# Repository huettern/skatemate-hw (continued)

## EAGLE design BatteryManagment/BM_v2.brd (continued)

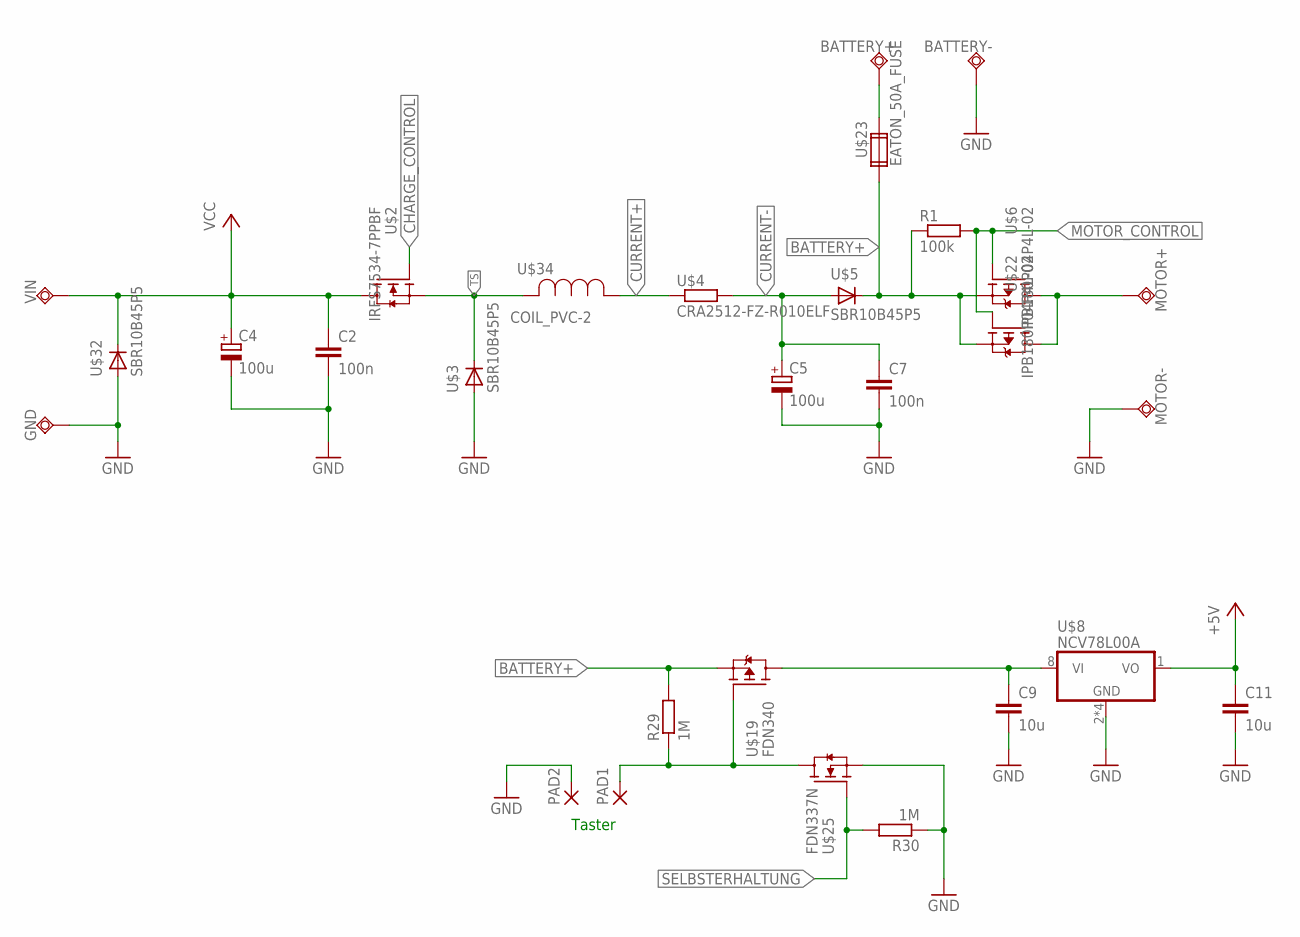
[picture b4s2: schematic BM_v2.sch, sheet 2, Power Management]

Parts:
BATTERY+: Battery+; TESTPAD
BATTERY-: Battery+; TESTPAD
C2, C7: 100n; C0603
C4, C5: 100u; E3,5-10
C9, C11: 10u; C0805
GND: Battery+; TESTPAD
MOTOR+: Battery+; TESTPAD
MOTOR-: PAD; TESTPAD
PAD1, PAD2: SMD5; SMD2,54-5,08
R1: 100k; R0603
R29, R30: 1M; R0603
U$2: IRFS7534-7PPBF; PG-TO263-7-3
U$3, U$5, U$32: SBR10B45P5; POWERDI-5
U$4: CRA2512-FZ-R010ELF; R2512
U$6, U$22: IPB180P04P4L-02; PG-TO263-7-3
U$8: NCV78L00A; SOIC8
U$19: FDN340; SOT23
U$23: EATON_50A_FUSE; LITTELFUSE
U$25: FDN337N; SOT23
U$34: COIL_PVC-2
VIN: Battery+; TESTPAD

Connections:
+5V: C11.1, U$8.1 (VO); also elsewhere on the board
BATTERY+: R1.1, R29.2, U$5.PAD (C), U$6.2 (S), U$6.3 (S), U$6.5 (S), U$6.6 (S), U$6.7 (S), U$19.2 (S), U$22.2 (S), U$22.3 (S), U$22.5 (S), U$22.6 (S), U$22.7 (S), U$23.P$1 (1A); also elsewhere on the board
CHARGE_CONTROL: U$2.1 (G); also elsewhere on the board
CURRENT+: U$4.1, U$34.P$1 (1); also elsewhere on the board
CURRENT-: C5.+, C7.1, U$4.2, U$5.L (A), U$5.R (A); also elsewhere on the board
GND: BATTERY-.P$1, C2.2, C4.-, C5.-, C7.2, C9.2, C11.2, GND.P$1, MOTOR-.P$1, PAD2.1, R30.1, U$3.L (A), U$3.R (A), U$8.2 (GND), U$8.3 (GND), U$8.6 (GND), U$8.7 (GND), U$25.2 (S), U$32.L (A), U$32.R (A); also elsewhere on the board
MOTOR+: MOTOR+.P$1, U$6.8 (D), U$22.8 (D)
MOTOR_CONTROL: R1.2, U$6.1 (G), U$22.1 (G); also elsewhere on the board
unnamed: PAD1.1, R29.1, U$19.1 (G), U$25.3 (D)
unnamed: BATTERY+.P$1, U$23.P$3 (2A)
SELBSTERHALTUNG: R30.2, U$25.1 (G); also elsewhere on the board
TEST: C9.1, U$8.8 (VI), U$19.3 (D)
TS: U$2.2 (S), U$2.3 (S), U$2.5 (S), U$2.6 (S), U$2.7 (S), U$3.PAD (C), U$34.P$2 (2); also elsewhere on the board
VCC: C2.1, C4.+, U$2.8 (D), U$32.PAD (C), VIN.P$1; also elsewhere on the board

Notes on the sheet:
Taster

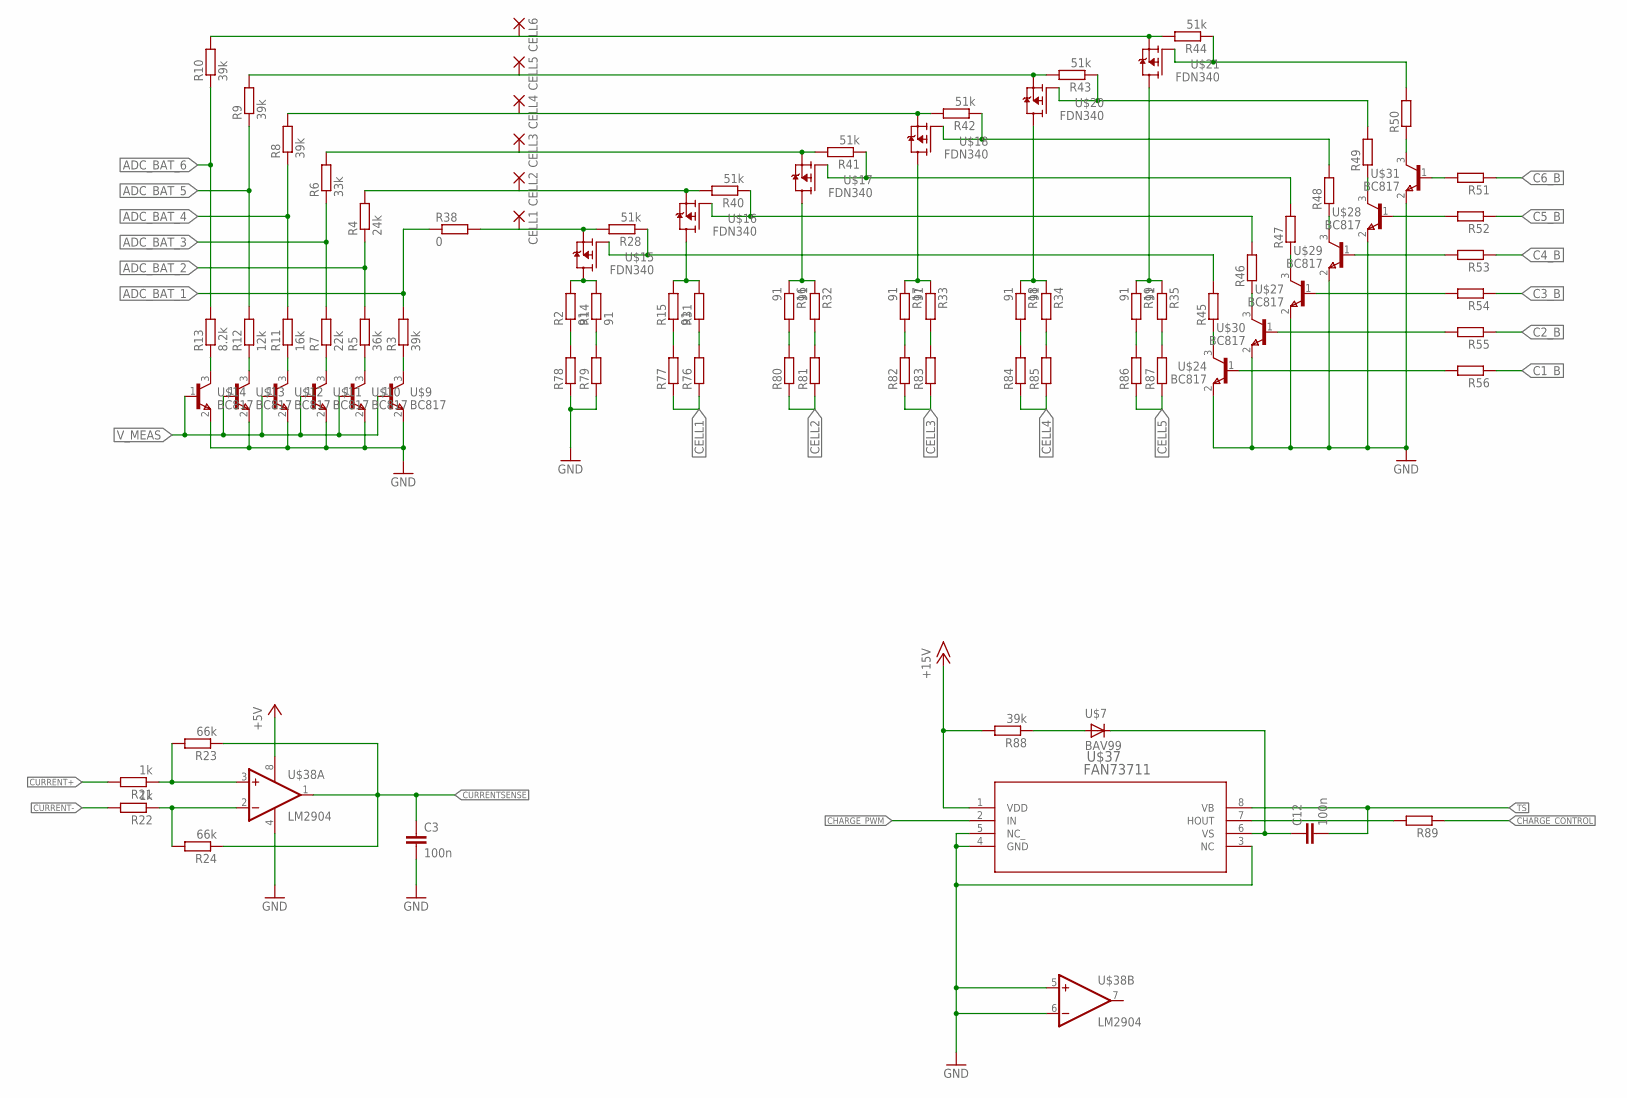
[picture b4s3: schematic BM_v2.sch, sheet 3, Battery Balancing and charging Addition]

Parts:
C3, C12: 100n; C0603
CELL1, CELL2, CELL3, CELL4, CELL5, CELL6: SMD5; SMD2,54-5,08
R2, R14, R15, R16, R17, R18, R19, R32, R33, R34, R35: 91; R0603
R3, R8, R9, R10, R88: 39k; R0603
R4: 24k; R0603
R5: 36k; R0603
R6: 33k; R0603
R7: 22k; R0603
R11: 16k; R0603
R12: 12k; R0603
R13: 8.2k; R0603
R21, R22: 1k; R0603
R23, R24: 66k; R0603
R28, R40, R41, R42, R43, R44: 51k; R0603
R31, R45, R46, R47, R48, R49, R50, R51, R52, R53, R54, R55, R56, R76, R77, R78, R79, R80, R81, R82, R83, R84, R85, R86, R87, R89: R-EU_R0603; R0603
R38: 0; R0603
U$7: BAV99; SOT23
U$9, U$10, U$11, U$12, U$13, U$14, U$24, U$27, U$28, U$29, U$30, U$31: BC817; SOT23
U$15, U$16, U$17, U$18, U$20, U$21: FDN340; SOT23
U$37: FAN73711; SOIC8
U$38: LM2904; SOIC8

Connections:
+5V: U$38.8 (V+); also elsewhere on the board
+15V: R88.2, U$37.1 (VDD); also elsewhere on the board
ADC_BAT_1: R3.2, R38.1; also elsewhere on the board
ADC_BAT_2: R4.1, R5.2; also elsewhere on the board
ADC_BAT_3: R6.1, R7.2; also elsewhere on the board
ADC_BAT_4: R8.1, R11.2; also elsewhere on the board
ADC_BAT_5: R9.1, R12.2; also elsewhere on the board
ADC_BAT_6: R10.1, R13.2; also elsewhere on the board
C1_B: R56.1; also elsewhere on the board
C2_B: R55.1; also elsewhere on the board
C3_B: R54.1; also elsewhere on the board
C4_B: R53.1; also elsewhere on the board
C5_B: R52.1; also elsewhere on the board
C6_B: R51.1; also elsewhere on the board
CELL1: CELL1.1, R28.2, R38.2, R76.1, R77.1, U$15.2 (S)
CELL2: CELL2.1, R4.2, R40.2, R80.1, R81.1, U$16.2 (S)
CELL3: CELL3.1, R6.2, R41.2, R82.1, R83.1, U$17.2 (S)
CELL4: CELL4.1, R8.2, R42.2, R84.1, R85.1, U$18.2 (S)
CELL5: CELL5.1, R9.2, R43.2, R86.1, R87.1, U$20.2 (S)
CELL6: CELL6.1, R10.2, R44.2, U$21.2 (S)
CHARGE_CONTROL: R89.1; also elsewhere on the board
CHARGE_PWM: U$37.2 (IN); also elsewhere on the board
CURRENT+: R21.2; also elsewhere on the board
CURRENT-: R22.2; also elsewhere on the board
CURRENTSENSE: C3.1, R23.1, R24.1, U$38.1 (OUT); also elsewhere on the board
GND: C3.2, R78.1, R79.1, U$9.2 (E), U$10.2 (E), U$11.2 (E), U$12.2 (E), U$13.2 (E), U$14.2 (E), U$24.2 (E), U$27.2 (E), U$28.2 (E), U$29.2 (E), U$30.2 (E), U$31.2 (E), U$37.3 (NC), U$37.4 (GND), U$37.5 (NC_), U$38.4 (V-), U$38.5 (+IN), U$38.6 (-IN); also elsewhere on the board
unnamed: C12.1, U$7.2 (C), U$37.6 (VS)
unnamed: R13.1, U$14.3 (C)
unnamed: R12.1, U$13.3 (C)
unnamed: R2.2, R14.2, U$15.3 (D)
unnamed: R15.2, R31.2, U$16.3 (D)
unnamed: R11.1, U$12.3 (C)
unnamed: R7.1, U$11.3 (C)
unnamed: R5.1, U$10.3 (C)
unnamed: R3.1, U$9.3 (C)
unnamed: R16.1, R32.1, U$17.3 (D)
unnamed: R17.1, R33.1, U$18.3 (D)
unnamed: R18.1, R34.1, U$20.3 (D)
unnamed: R19.1, R35.1, U$21.3 (D)
unnamed: R21.1, R23.2, U$38.3 (+IN)
unnamed: R22.1, R24.2, U$38.2 (-IN)
unnamed: R28.1, R45.2, U$15.1 (G)
unnamed: R40.1, R46.2, U$16.1 (G)
unnamed: R41.1, R47.2, U$17.1 (G)
unnamed: R42.1, R48.2, U$18.1 (G)
unnamed: R43.1, R49.2, U$20.1 (G)
unnamed: R44.1, R50.2, U$21.1 (G)
unnamed: R49.1, U$28.3 (C)
unnamed: R50.1, U$31.3 (C)
unnamed: R48.1, U$29.3 (C)
unnamed: R47.1, U$27.3 (C)
unnamed: R46.1, U$30.3 (C)
unnamed: R45.1, U$24.3 (C)
unnamed: R51.2, U$31.1 (B)
unnamed: R52.2, U$28.1 (B)
unnamed: R53.2, U$29.1 (B)
unnamed: R54.2, U$27.1 (B)
unnamed: R55.2, U$30.1 (B)
unnamed: R56.2, U$24.1 (B)
unnamed: R15.1, R77.2
unnamed: R31.1, R76.2
unnamed: R2.1, R78.2
unnamed: R14.1, R79.2
unnamed: R16.2, R80.2
unnamed: R32.2, R81.2
unnamed: R17.2, R82.2
unnamed: R33.2, R83.2
unnamed: R18.2, R84.2
unnamed: R34.2, R85.2
unnamed: R19.2, R86.2
unnamed: R35.2, R87.2
unnamed: R88.1, U$7.1 (A)
unnamed: R89.2, U$37.7 (HOUT)
TS: C12.2, U$37.8 (VB); also elsewhere on the board
V_MEAS: U$9.1 (B), U$10.1 (B), U$11.1 (B), U$12.1 (B), U$13.1 (B), U$14.1 (B); also elsewhere on the board

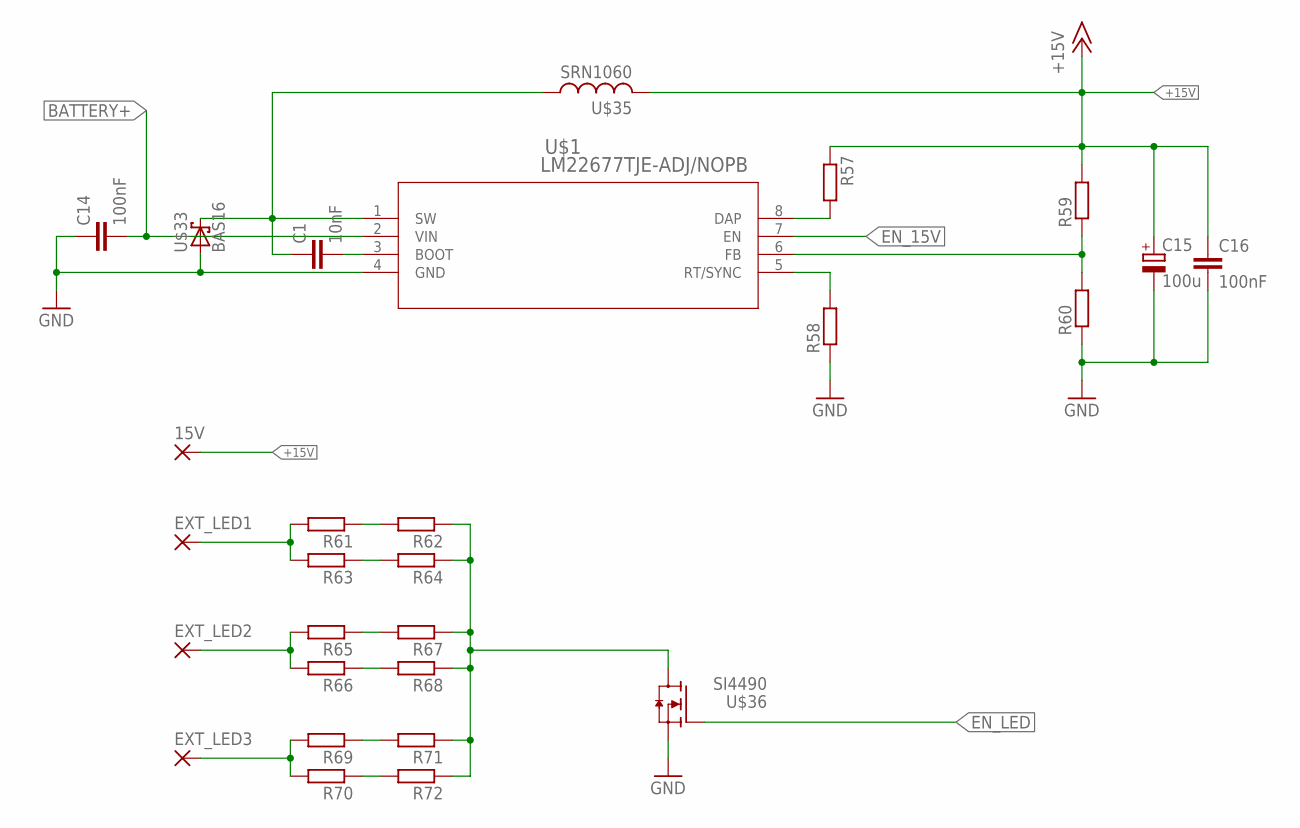
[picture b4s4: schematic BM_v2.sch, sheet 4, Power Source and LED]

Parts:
15V: SMD5; SMD2,54-5,08
C1: 10nF; C0603
C14, C16: 100nF; C0603
C15: 100u; E3,5-10
EXT_LED1, EXT_LED2, EXT_LED3: SMD5; SMD2,54-5,08
R57, R58, R59, R60, R61, R62, R63, R64, R65, R66, R67, R68, R69, R70, R71, R72: R-EU_R0603; R0603
U$1: LM22677TJE-ADJ/NOPB; TJ7A
U$33: BAS16; SOT23
U$35: SRN1060
U$36: SI4490; SOIC8

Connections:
+15V: 15V.1, C15.+, C16.1, R57.1, R59.2, U$35.P$2 (2); also elsewhere on the board
BATTERY+: C14.2, U$1.2 (VIN); also elsewhere on the board
EN_15V: U$1.7 (EN); also elsewhere on the board
EN_LED: U$36.4 (G); also elsewhere on the board
FEEDBACK: R59.1, R60.2, U$1.6 (FB)
GND: C14.1, C15.-, C16.2, R58.1, R60.1, U$1.4 (GND), U$33.1 (A), U$36.1 (S), U$36.2 (S), U$36.3 (S); also elsewhere on the board
unnamed: C1.2, U$1.3 (BOOT)
unnamed: C1.1, U$1.1 (SW), U$33.3 (C), U$35.P$1 (1)
unnamed: R57.2, U$1.8 (DAP)
unnamed: R58.2, U$1.5 (RT/SYNC)
unnamed: EXT_LED1.1, R61.2, R63.2
unnamed: R61.1, R62.2
unnamed: R63.1, R64.2
unnamed: EXT_LED2.1, R65.2, R66.2
unnamed: R65.1, R67.2
unnamed: R66.1, R68.2
unnamed: R62.1, R64.1, R67.1, R68.1, R71.1, R72.1, U$36.5 (D), U$36.6 (D), U$36.7 (D), U$36.8 (D)
unnamed: EXT_LED3.1, R69.2, R70.2
unnamed: R69.1, R71.2
unnamed: R70.1, R72.2

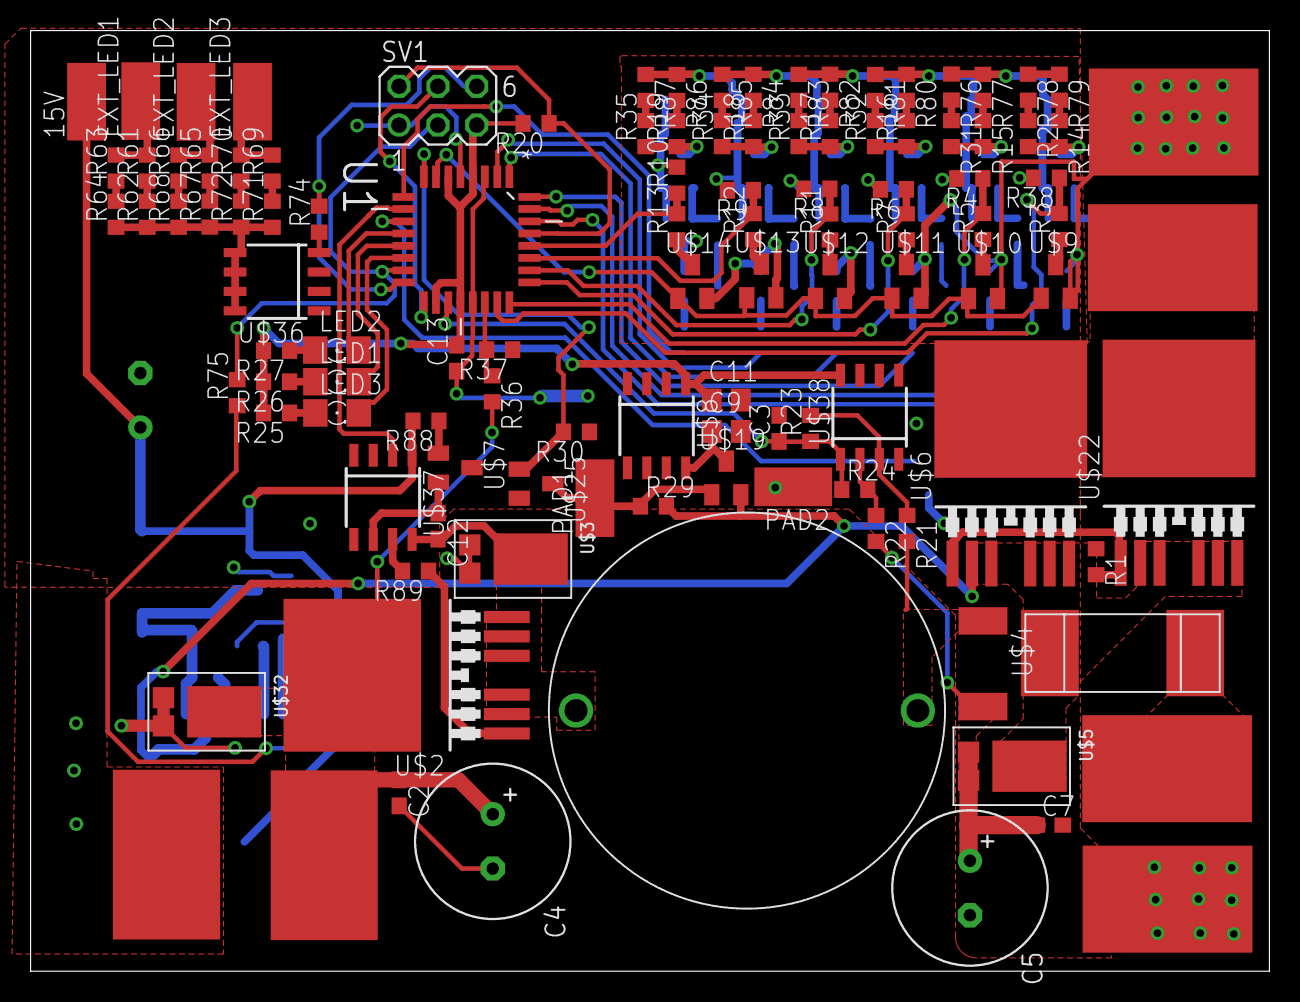
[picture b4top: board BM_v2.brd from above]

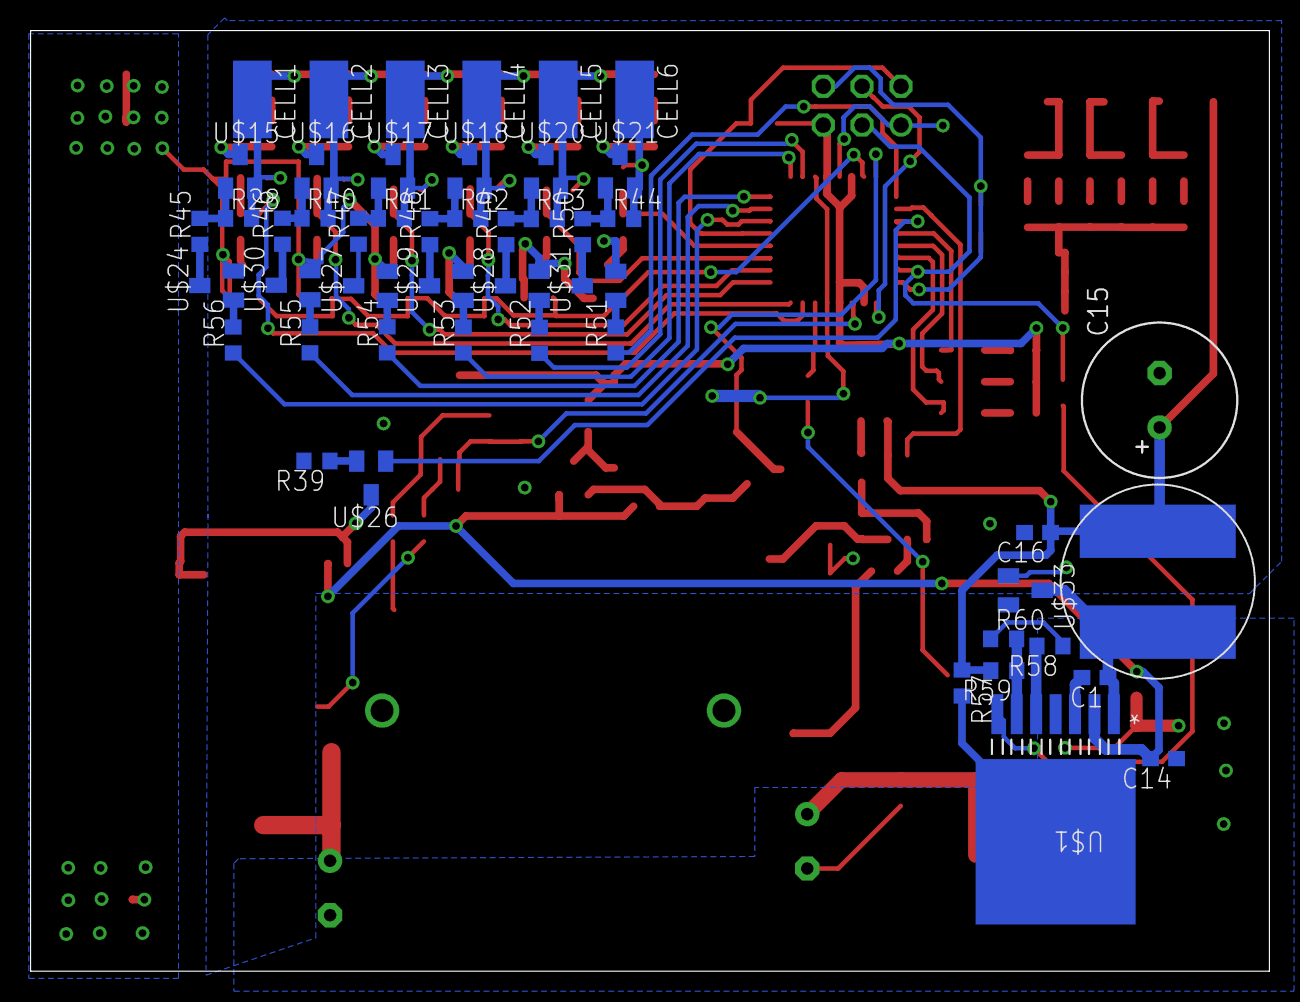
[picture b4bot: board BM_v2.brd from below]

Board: 2 copper layers, 81.0 x 61.5 mm, 162 parts (49 on the bottom side), 113 nets.

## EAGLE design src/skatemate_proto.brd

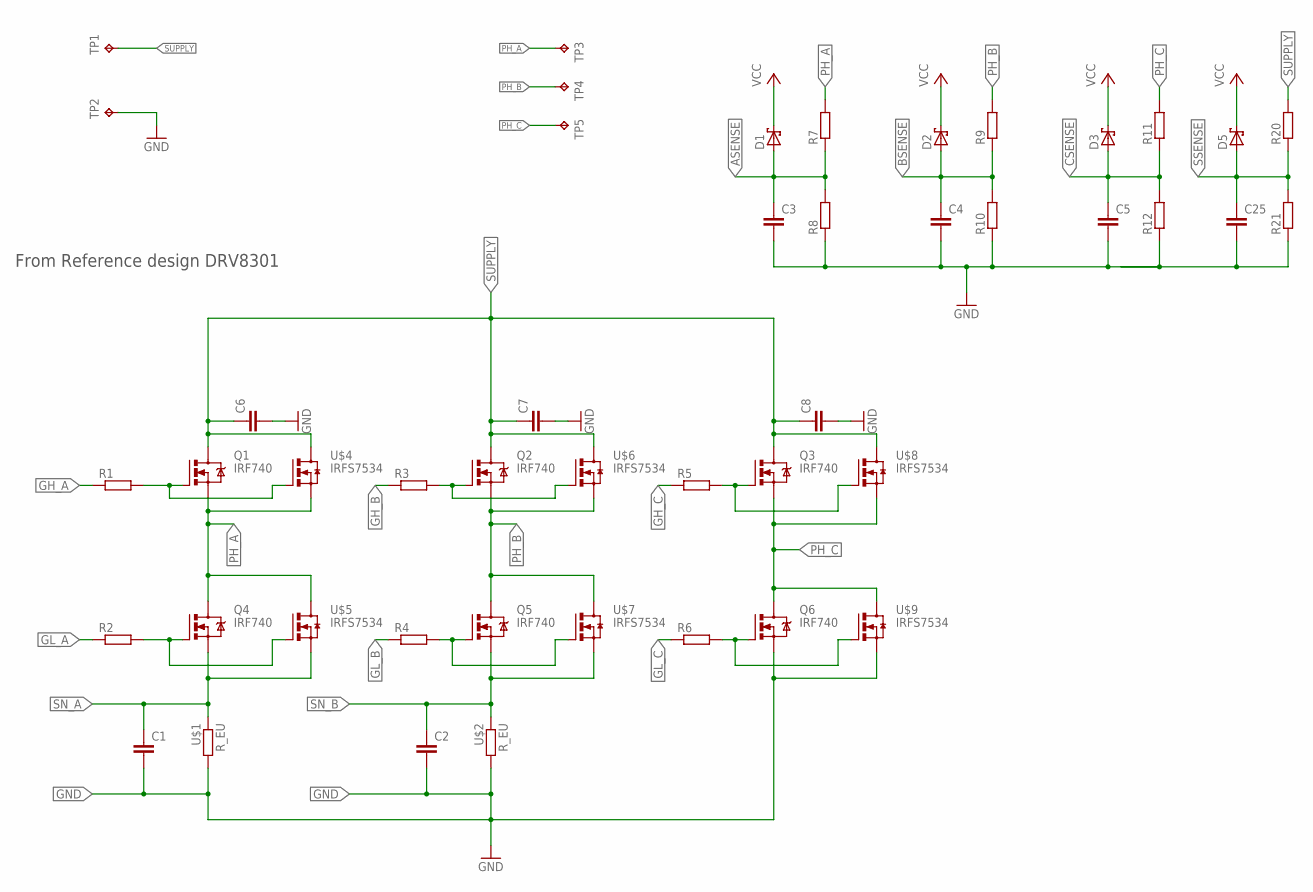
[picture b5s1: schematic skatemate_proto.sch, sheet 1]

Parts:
C1, C2, C3, C4, C5, C25: C-EUC0805; C0805
C6, C7, C8: C-EUC1206; C1206
D1, D2, D3, D5: SCHOTTKY-DIODESOD80C; SOD80C
Q1, Q2, Q3, Q4, Q5, Q6: IRF740; TO220BV
R1, R2, R3, R4, R5, R6, R7, R8, R9, R10, R11, R12, R20, R21: R-EU_R0805; R0805
TP1, TP2, TP3, TP4, TP5: TPSMD_M_1006; SMD_M_1006
U$1, U$2: R_EU; R2512
U$4, U$5, U$6, U$7, U$8, U$9: IRFS7534; D2PAK-7

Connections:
ASENSE: C3.1, D1.A, R7.1, R8.2; also elsewhere on the board
BSENSE: C4.1, D2.A, R9.1, R10.2; also elsewhere on the board
CSENSE: C5.1, D3.A, R11.1, R12.2; also elsewhere on the board
GH_A: R1.1; also elsewhere on the board
GH_B: R3.1; also elsewhere on the board
GH_C: R5.1; also elsewhere on the board
GL_A: R2.1; also elsewhere on the board
GL_B: R4.1; also elsewhere on the board
GL_C: R6.1; also elsewhere on the board
GND: C1.2, C2.2, C3.2, C4.2, C5.2, C6.2, C7.2, C8.2, C25.2, Q6.S, R8.1, R10.1, R12.1, R21.1, TP2.P$1, U$1.2, U$2.2, U$9.S1 (S), U$9.S2 (S), U$9.S3 (S), U$9.S4 (S), U$9.S5 (S); also elsewhere on the board
unnamed: Q1.G, R1.2, U$4.G
unnamed: Q4.G, R2.2, U$5.G
unnamed: Q5.G, R4.2, U$7.G
unnamed: Q2.G, R3.2, U$6.G
unnamed: Q3.G, R5.2, U$8.G
unnamed: Q6.G, R6.2, U$9.G
PH_A: Q1.S, Q4.D, R7.2, TP3.P$1, U$4.S1 (S), U$4.S2 (S), U$4.S3 (S), U$4.S4 (S), U$4.S5 (S), U$5.D; also elsewhere on the board
PH_B: Q2.S, Q5.D, R9.2, TP4.P$1, U$6.S1 (S), U$6.S2 (S), U$6.S3 (S), U$6.S4 (S), U$6.S5 (S), U$7.D; also elsewhere on the board
PH_C: Q3.S, Q6.D, R11.2, TP5.P$1, U$8.S1 (S), U$8.S2 (S), U$8.S3 (S), U$8.S4 (S), U$8.S5 (S), U$9.D; also elsewhere on the board
SN_A: C1.1, Q4.S, U$1.1, U$5.S1 (S), U$5.S2 (S), U$5.S3 (S), U$5.S4 (S), U$5.S5 (S); also elsewhere on the board
SN_B: C2.1, Q5.S, U$2.1, U$7.S1 (S), U$7.S2 (S), U$7.S3 (S), U$7.S4 (S), U$7.S5 (S); also elsewhere on the board
SSENSE: C25.1, D5.A, R20.1, R21.2; also elsewhere on the board
SUPPLY: C6.1, C7.1, C8.1, Q1.D, Q2.D, Q3.D, R20.2, TP1.P$1, U$4.D, U$6.D, U$8.D; also elsewhere on the board
VCC: D1.C, D2.C, D3.C, D5.C; also elsewhere on the board

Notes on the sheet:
From Reference design DRV8301

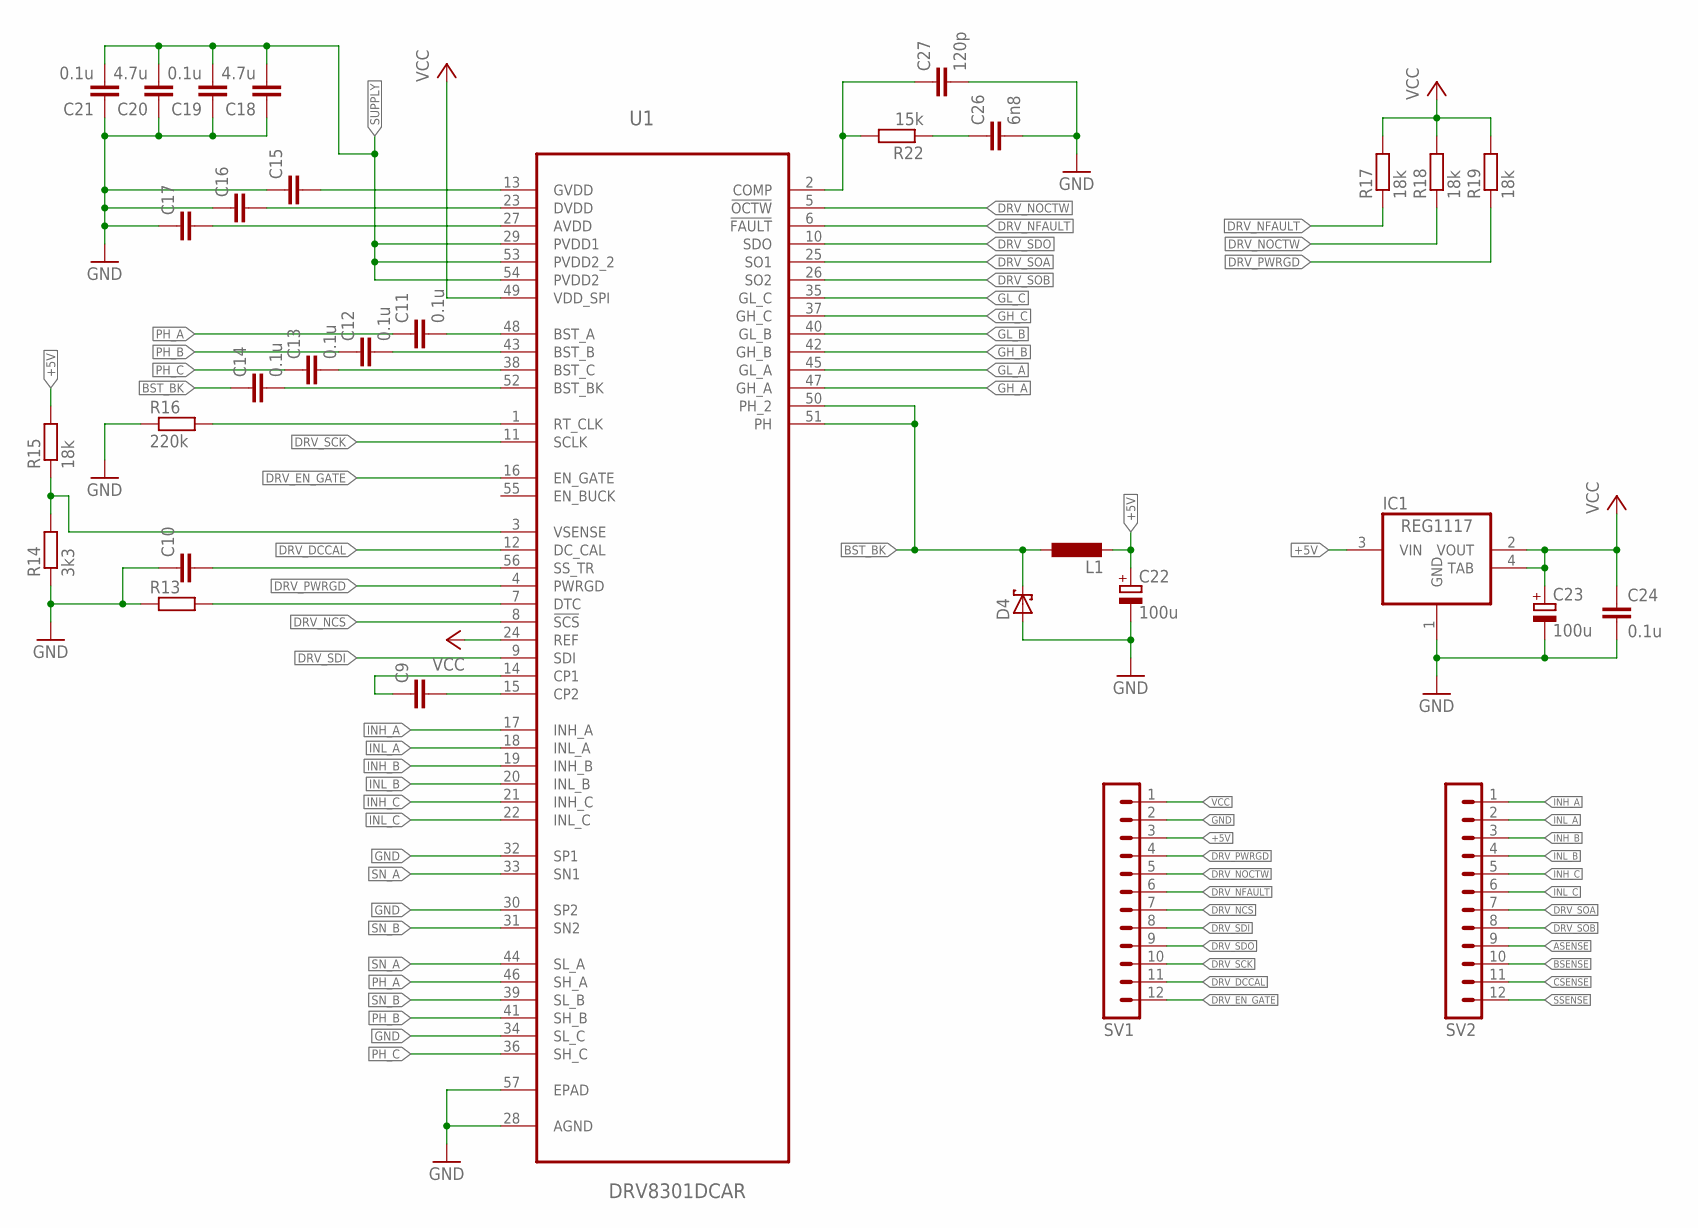
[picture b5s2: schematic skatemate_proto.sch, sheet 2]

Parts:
C9, C10, C15, C16, C17: C-EUC0805; C0805
C11, C12, C13, C14, C19, C21, C24: 0.1u; C0805
C18, C20: 4.7u; C0805
C22, C23: 100u; B/3528-21W
C26: 6n8; C0805
C27: 120p; C0805
D4: SCHOTTKY-DIODEDO-214AA; DO-214AA
IC1: REG1117; SOT223
L1: L-EUSDR0805; SDR0805
R13: R-EU_R0805; R0805
R14: 3k3; R0805
R15, R17, R18, R19: 18k; R0805
R16: 220k; R0805
R22: 15k; R0805
SV1, SV2: MA12-1
U1: DRV8301DCAR; SOP50P810X120-57N

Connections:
+5V: C22.+, IC1.3 (VIN), L1.2, R15.2, SV1.3
ASENSE: SV2.9; also elsewhere on the board
BSENSE: SV2.10; also elsewhere on the board
BST_BK: C14.1, D4.C, L1.1, U1.50 (PH_2), U1.51 (PH)
CSENSE: SV2.11; also elsewhere on the board
DRV_DCCAL: SV1.11, U1.12 (DC_CAL); also elsewhere on the board
DRV_EN_GATE: SV1.12, U1.16 (EN_GATE); also elsewhere on the board
DRV_NCS: SV1.7, U1.8 (!SCS); also elsewhere on the board
DRV_NFAULT: R17.1, SV1.6, U1.6 (!FAULT); also elsewhere on the board
DRV_NOCTW: R18.1, SV1.5, U1.5 (!OCTW); also elsewhere on the board
DRV_PWRGD: R19.1, SV1.4, U1.4 (PWRGD); also elsewhere on the board
DRV_SCK: SV1.10, U1.11 (SCLK); also elsewhere on the board
DRV_SDI: SV1.8, U1.9 (SDI); also elsewhere on the board
DRV_SDO: SV1.9, U1.10 (SDO); also elsewhere on the board
DRV_SOA: SV2.7, U1.25 (SO1); also elsewhere on the board
DRV_SOB: SV2.8, U1.26 (SO2); also elsewhere on the board
GH_A: U1.47 (GH_A); also elsewhere on the board
GH_B: U1.42 (GH_B); also elsewhere on the board
GH_C: U1.37 (GH_C); also elsewhere on the board
GL_A: U1.45 (GL_A); also elsewhere on the board
GL_B: U1.40 (GL_B); also elsewhere on the board
GL_C: U1.35 (GL_C); also elsewhere on the board
GND: C10.1, C15.1, C16.1, C17.1, C18.1, C19.1, C20.1, C21.1, C22.-, C23.-, C24.2, C26.2, C27.2, D4.A, IC1.1 (GND), R13.1, R14.1, R16.1, SV1.2, U1.28 (AGND), U1.30 (SP2), U1.32 (SP1), U1.34 (SL_C), U1.57 (EPAD); also elsewhere on the board
INH_A: SV2.1, U1.17 (INH_A); also elsewhere on the board
INH_B: SV2.3, U1.19 (INH_B); also elsewhere on the board
INH_C: SV2.5, U1.21 (INH_C); also elsewhere on the board
INL_A: SV2.2, U1.18 (INL_A); also elsewhere on the board
INL_B: SV2.4, U1.20 (INL_B); also elsewhere on the board
INL_C: SV2.6, U1.22 (INL_C); also elsewhere on the board
unnamed: C9.2, U1.15 (CP2)
unnamed: C9.1, U1.14 (CP1)
unnamed: R13.2, U1.7 (DTC)
unnamed: R14.2, R15.1, U1.3 (VSENSE)
unnamed: C10.2, U1.56 (SS_TR)
unnamed: R16.2, U1.1 (RT_CLK)
unnamed: C11.2, U1.48 (BST_A)
unnamed: C12.2, U1.43 (BST_B)
unnamed: C13.2, U1.38 (BST_C)
unnamed: C14.2, U1.52 (BST_BK)
unnamed: C15.2, U1.13 (GVDD)
unnamed: C16.2, U1.23 (DVDD)
unnamed: C17.2, U1.27 (AVDD)
unnamed: C27.1, R22.2, U1.2 (COMP)
unnamed: C26.1, R22.1
PH_A: C11.1, U1.46 (SH_A); also elsewhere on the board
PH_B: C12.1, U1.41 (SH_B); also elsewhere on the board
PH_C: C13.1, U1.36 (SH_C); also elsewhere on the board
SN_A: U1.33 (SN1), U1.44 (SL_A); also elsewhere on the board
SN_B: U1.31 (SN2), U1.39 (SL_B); also elsewhere on the board
SSENSE: SV2.12; also elsewhere on the board
SUPPLY: C18.2, C19.2, C20.2, C21.2, U1.29 (PVDD1), U1.53 (PVDD2_2), U1.54 (PVDD2); also elsewhere on the board
VCC: C23.+, C24.1, IC1.2 (VOUT), IC1.4 (TAB), R17.2, R18.2, R19.2, SV1.1, U1.24 (REF), U1.49 (VDD_SPI); also elsewhere on the board

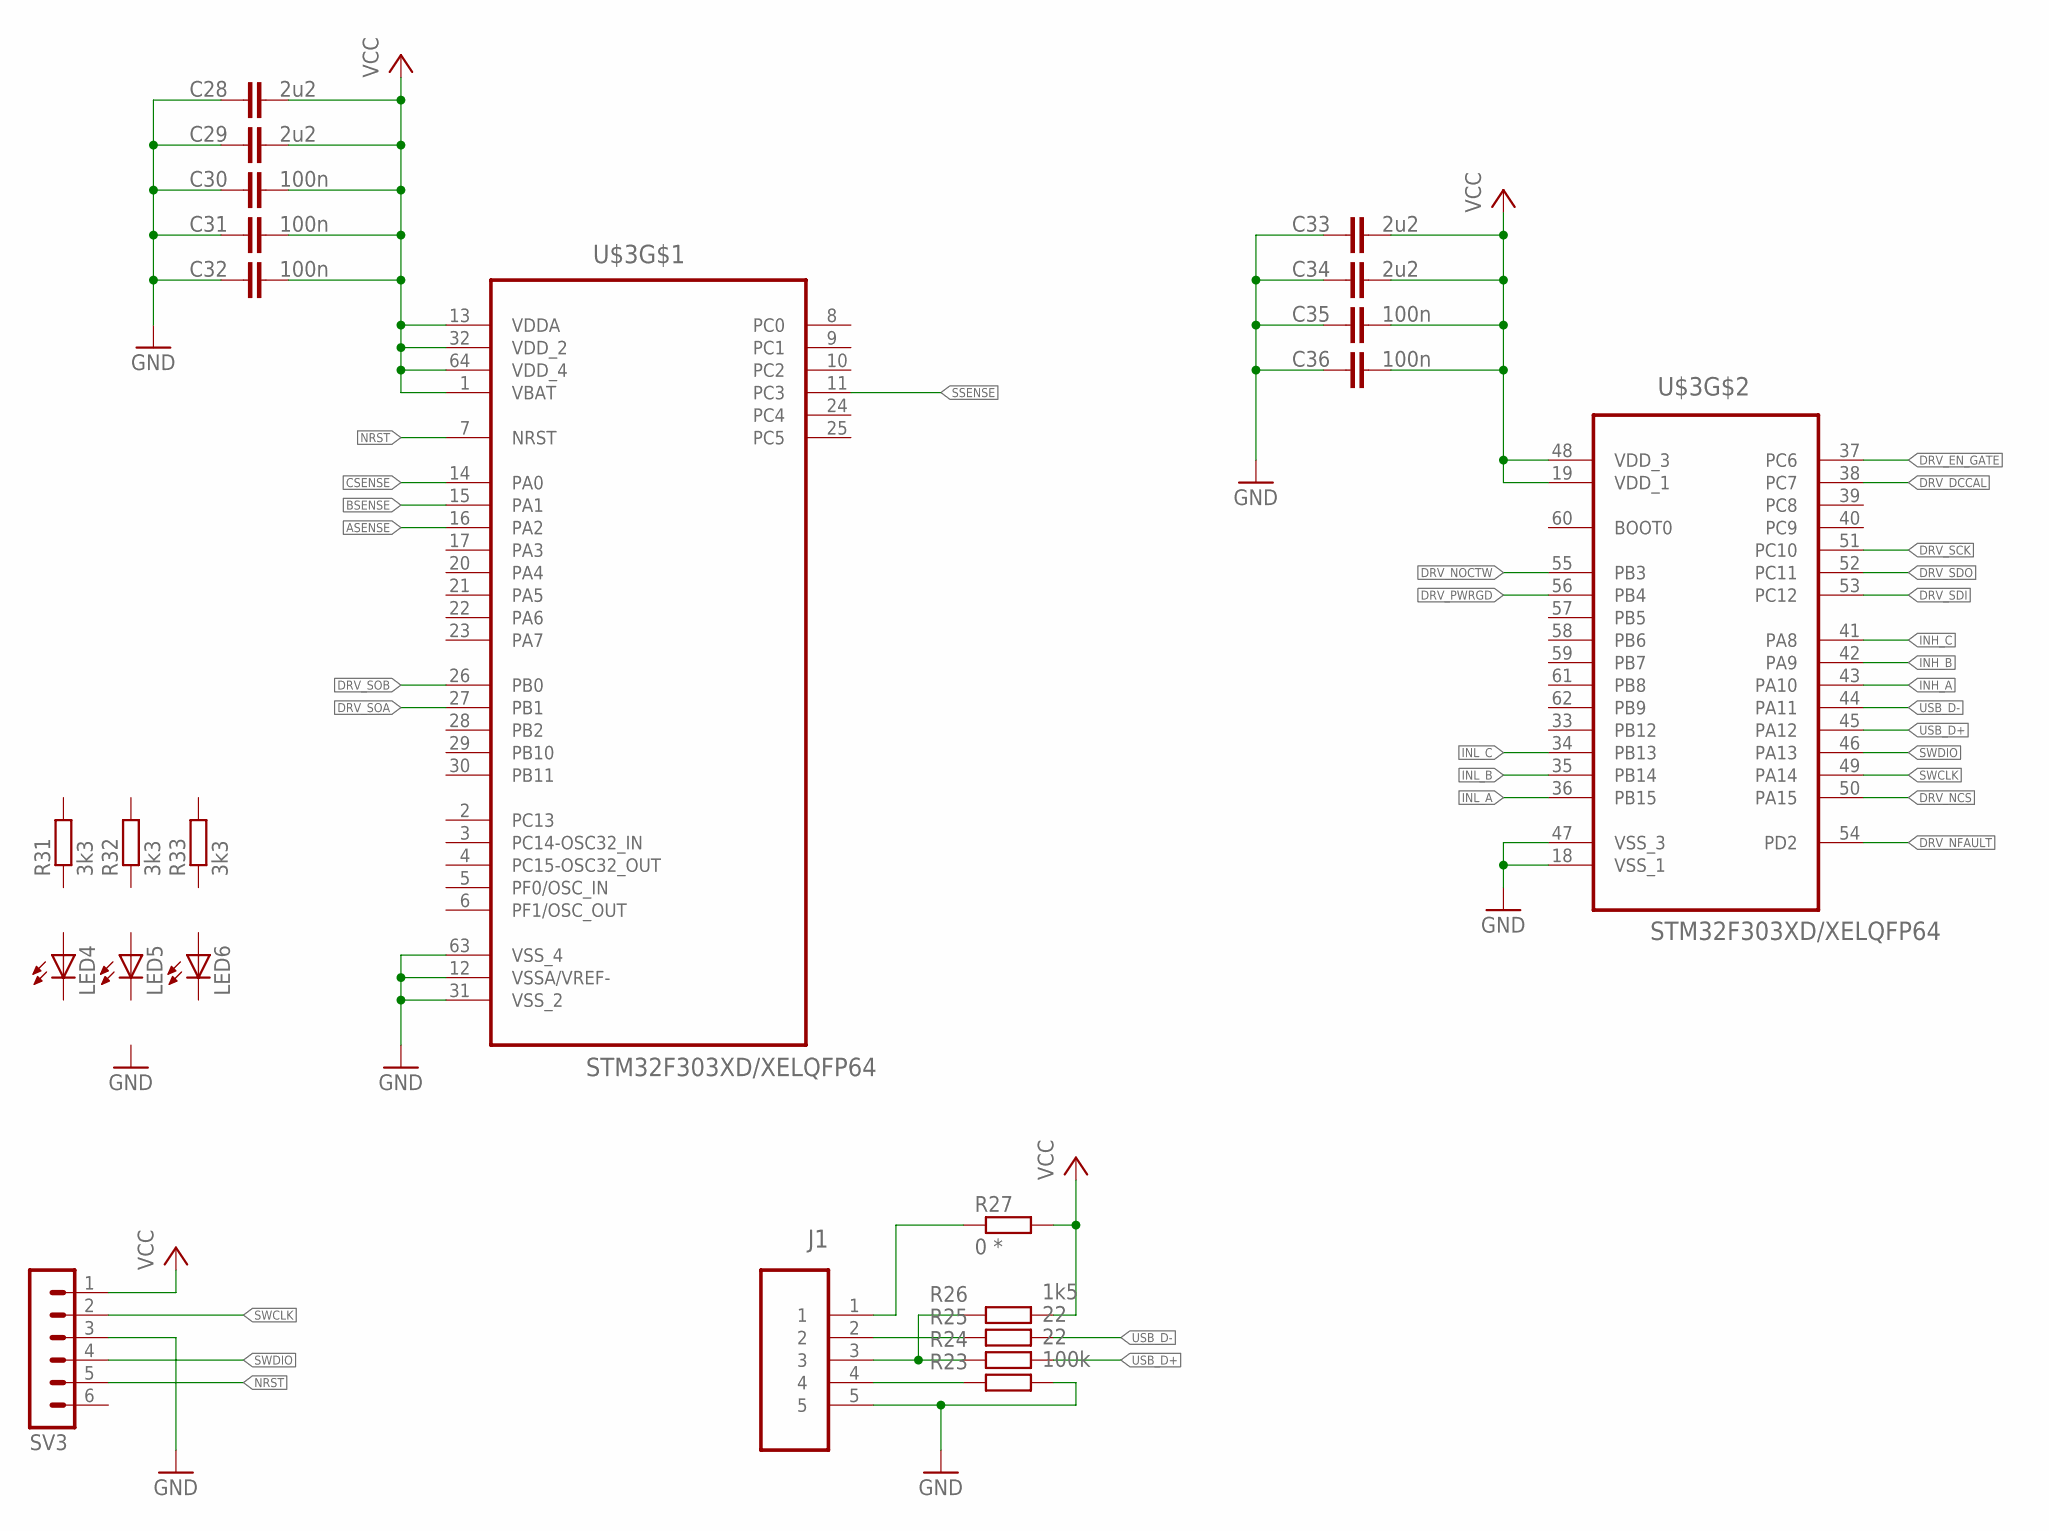
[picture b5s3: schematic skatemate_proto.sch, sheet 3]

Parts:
C28, C29, C33, C34: 2u2; C0805
C30, C31, C32, C35, C36: 100n; C0805
J1: 47346-0001; MOLEX_47346-0001
LED4, LED5, LED6: LEDCHIP-LED0805; CHIP-LED0805
R23: 100k; R0805
R24, R25: 22; R0805
R26: 1k5; R0805
R27: 0 *; R0805
R31, R32, R33: 3k3; R0805
SV3: MA06-1
U$3: STM32F303XD/XELQFP64; LQFP64

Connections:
ASENSE: U$3.16 (PA2); also elsewhere on the board
BSENSE: U$3.15 (PA1); also elsewhere on the board
CSENSE: U$3.14 (PA0); also elsewhere on the board
DRV_DCCAL: U$3.38 (PC7); also elsewhere on the board
DRV_EN_GATE: U$3.37 (PC6); also elsewhere on the board
DRV_NCS: U$3.50 (PA15); also elsewhere on the board
DRV_NFAULT: U$3.54 (PD2); also elsewhere on the board
DRV_NOCTW: U$3.55 (PB3); also elsewhere on the board
DRV_PWRGD: U$3.56 (PB4); also elsewhere on the board
DRV_SCK: U$3.51 (PC10); also elsewhere on the board
DRV_SDI: U$3.53 (PC12); also elsewhere on the board
DRV_SDO: U$3.52 (PC11); also elsewhere on the board
DRV_SOA: U$3.27 (PB1); also elsewhere on the board
DRV_SOB: U$3.26 (PB0); also elsewhere on the board
GND: C28.1, C29.1, C30.1, C31.1, C32.1, C33.1, C34.1, C35.1, C36.1, J1.5, R23.2, SV3.3, U$3.12 (VSSA/VREF-), U$3.18 (VSS_1), U$3.31 (VSS_2), U$3.47 (VSS_3), U$3.63 (VSS_4); also elsewhere on the board
INH_A: U$3.43 (PA10); also elsewhere on the board
INH_B: U$3.42 (PA9); also elsewhere on the board
INH_C: U$3.41 (PA8); also elsewhere on the board
INL_A: U$3.36 (PB15); also elsewhere on the board
INL_B: U$3.35 (PB14); also elsewhere on the board
INL_C: U$3.34 (PB13); also elsewhere on the board
unnamed: J1.4, R23.1
unnamed: J1.3, R24.1, R26.1
unnamed: J1.2, R25.1
unnamed: J1.1, R27.1
NRST: SV3.5, U$3.7 (NRST)
SSENSE: U$3.11 (PC3); also elsewhere on the board
SWCLK: SV3.2, U$3.49 (PA14)
SWDIO: SV3.4, U$3.46 (PA13)
USB_D+: R24.2, U$3.45 (PA12)
USB_D-: R25.2, U$3.44 (PA11)
VCC: C28.2, C29.2, C30.2, C31.2, C32.2, C33.2, C34.2, C35.2, C36.2, R26.2, R27.2, SV3.1, U$3.1 (VBAT), U$3.13 (VDDA), U$3.19 (VDD_1), U$3.32 (VDD_2), U$3.48 (VDD_3), U$3.64 (VDD_4); also elsewhere on the board
